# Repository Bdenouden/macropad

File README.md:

# macropad
This repo contains the design files for a macro pad based on 
- [https://www.thingiverse.com/thing:4765312](https://www.thingiverse.com/thing:4765312)
- [https://www.thingiverse.com/thing:4605764](https://www.thingiverse.com/thing:4605764)

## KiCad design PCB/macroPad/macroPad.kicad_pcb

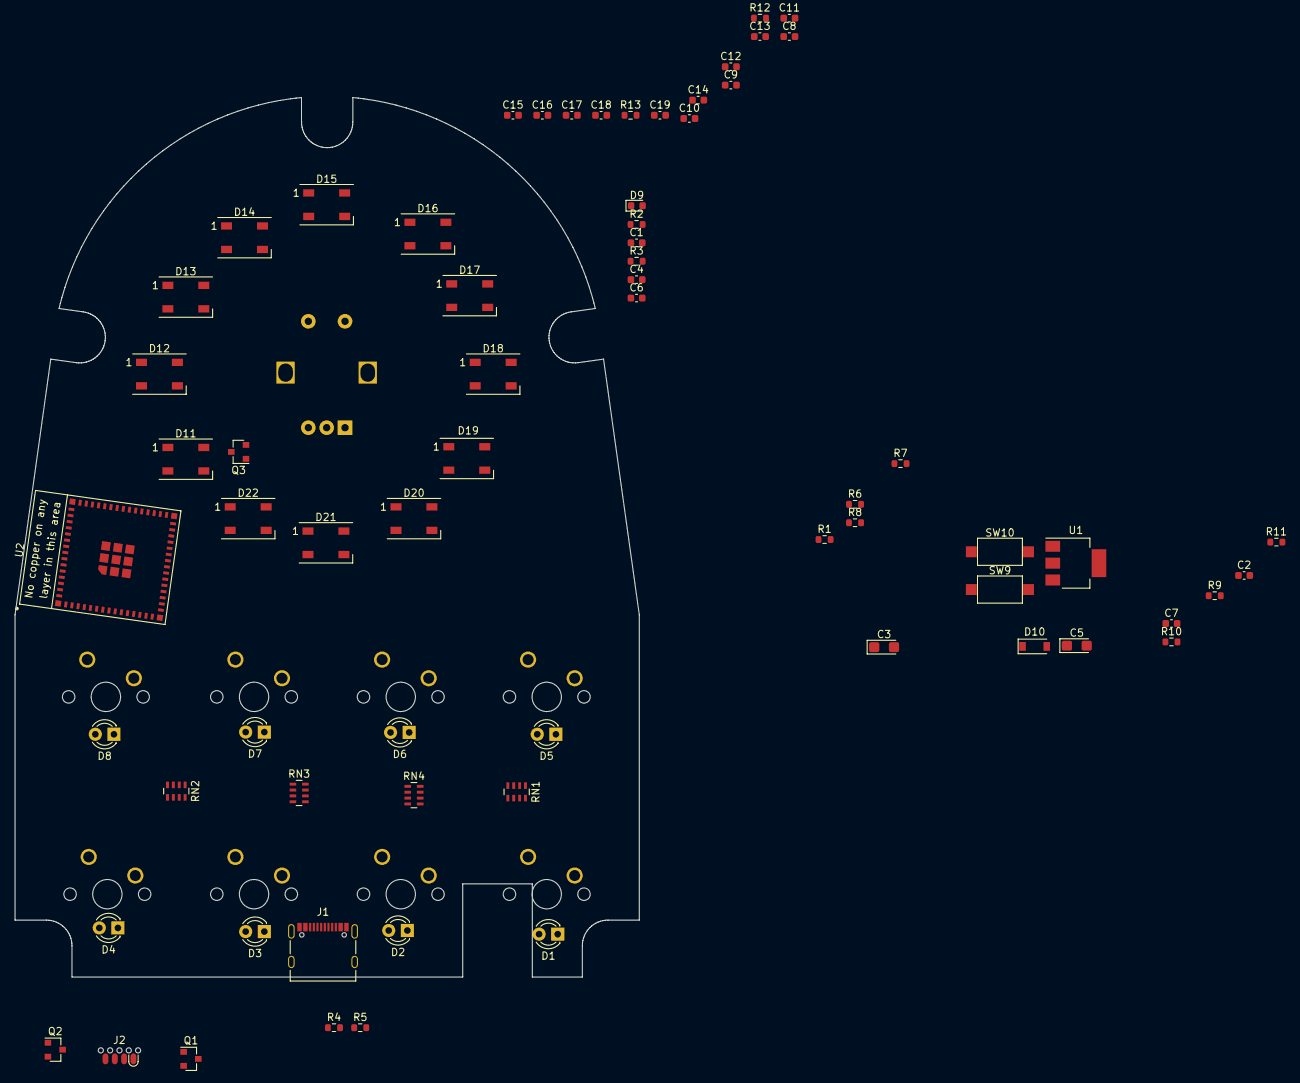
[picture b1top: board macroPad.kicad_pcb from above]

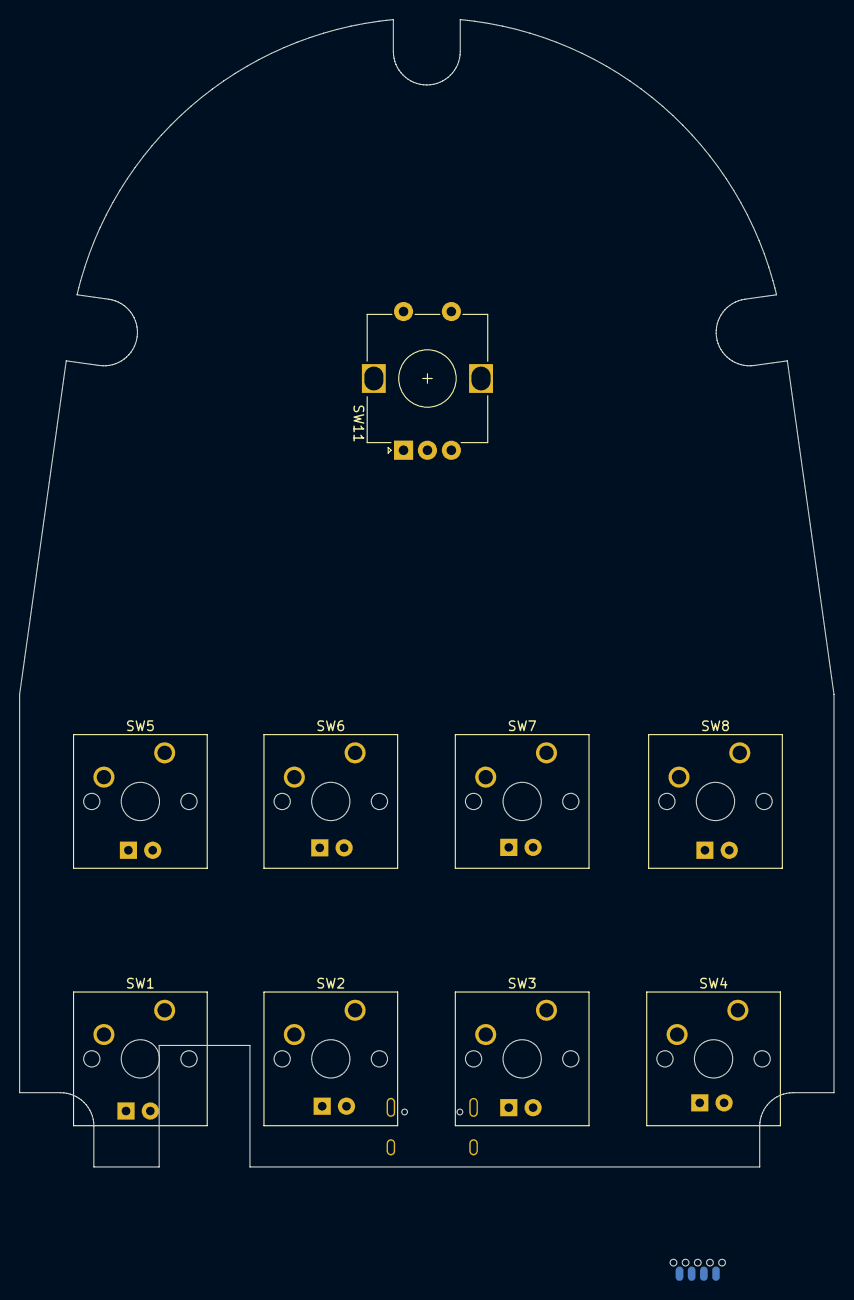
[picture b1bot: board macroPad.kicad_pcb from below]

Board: 2 copper layers, 85.1 x 119.9 mm, 76 parts (9 on the bottom side), 61 nets, no tracks yet.

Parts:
C1, C2, C6, C7: 0.1uF; C_0603_1608Metric
C3, C5: 22uF; CP_EIA-3216-10_Kemet-I
C4: 22uF; C_0603_1608Metric
C8, C9, C10, C11, C12, C13, C14, C15, C16, C17, C18, C19: 100nF; C_0603_1608Metric
D1, D2, D3, D4, D5, D6, D7, D8: LED; LED_D3.0mm
D9: POWER; LED_0603_1608Metric
D10: BAT760-7; D_SOD-123
D11, D12, D13, D14, D15, D16, D17, D18, D19, D20, D21, D22: WS2812B; LED_WS2812B_PLCC4_5.0x5.0mm_P3.2mm
J1: USB_C_Receptacle_USB2.0; USB_C_Receptacle_Palconn_UTC16-G
J2: SoicBite; SOIC_clipProgSmall
Q1, Q2: SS8050-G; SOT-23
Q3: BSS138; SOT-23
R1: 47; R_0603_1608Metric
R2, R3, R6, R9, R10, R12, R13: 10k; R_0603_1608Metric
R4, R5: 5k1; R_0603_1608Metric
R7, R8, R11: 100k; R_0603_1608Metric
RN1, RN2: 8R2; R_Array_Concave_4x0603
RN3, RN4: 10k; R_Array_Concave_4x0603
SW1, SW2, SW3, SW4, SW5, SW6, SW7, SW8: SW_cherry; SW_Cherry_MX_1.00u_PCB
SW9, SW10: SW_Push; SW_SPST_CK_RS282G05A3
SW11: Rotary_Encoder_Switch; RotaryEncoder_Alps_EC12E-Switch_Vertical_H20mm
U1: AMS1117-3.3; SOT-223-3_TabPin2
U2: ESP32-S2-MINI-1

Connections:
+3V3: C4.1, C5.1, C6.1, D1.2, D2.2, D3.2, D4.2, D5.2, D6.2, D7.2, D8.2, J2.1, Q3.1, R1.1, R6.2, R11.1, R12.2, SW1.1, SW2.1, SW3.1, SW4.1, SW5.2, SW6.2, SW7.2, SW8.2, U1.2, U2.3
/DTR: J2.5, Q2.3, R9.2
/EN: Q1.2, R2.1, U2.45
/IO0: C7.1, Q2.2, R3.1, R6.1, U2.4
/K1: RN4.1, SW1.2, U2.19
/K2: RN4.2, SW2.2, U2.15
/K3: RN4.3, SW3.2, U2.11
/K4: RN4.4, SW4.2, U2.7
/K5: RN3.8, SW5.1, U2.17
/K6: RN3.7, SW6.1, U2.13
/K7: RN3.6, SW7.1, U2.9
/K8: RN3.5, SW8.1, U2.5
/L1: RN1.8, U2.20
/L2: RN1.7, U2.16
/L3: RN1.6, U2.12
/L4: RN1.5, U2.8
/L5: RN2.8, U2.18
/L6: RN2.7, U2.14
/L7: RN2.6, U2.10
/L8: RN2.5, U2.6
/LED_DATA: Q3.2, R12.1
/ROT_CLK: R7.2, U2.32
/ROT_DT: R8.2, U2.33
/ROT_SW: R11.2, SW11.S1, U2.31
/RTS: J2.8, Q1.3, R10.2
/RX: J2.7, U2.40
/TX: J2.6, U2.39
/USB_D+: J1.A6, J1.B6, J2.3, U2.24
/USB_D-: J1.A7, J1.B7, J2.2, U2.23
/VBUS: C3.1, C8.1, C9.1, C10.1, C11.1, C12.1, C13.1, C14.1, C15.1, C16.1, C17.1, C18.1, C19.1, D10.1, D11.1, D12.1, D13.1, D14.1, D15.1, D16.1, D17.1, D18.1, D19.1, D20.1, D21.1, D22.1, R13.2, U1.3
/ledring/DIN_VCC: D11.4, Q3.3, R13.1
GND: C1.1, C2.1, C3.2, C4.2, C5.2, C6.2, C7.2, C8.2, C9.2, C10.2, C11.2, C12.2, C13.2, C14.2, C15.2, C16.2, C17.2, C18.2, C19.2, D9.1, D11.3, D12.3, D13.3, D14.3, D15.3, D16.3, D17.3, D18.3, D19.3, D20.3, D21.3, D22.3, J1.A1, J1.A12, J1.B1, J1.B12, J2.4, R4.1, R5.1, RN3.1, RN3.2, RN3.3, RN3.4, RN4.5, RN4.6, RN4.7, RN4.8, SW9.1, SW10.1, SW11.C, SW11.S2, U1.1, U2.1, U2.2, U2.30, U2.42, U2.43, U2.46, U2.47, U2.48, U2.49, U2.50, U2.51, U2.52, U2.53, U2.54, U2.55, U2.56, U2.57, U2.58, U2.59, U2.60, U2.61, U2.62, U2.63, U2.64, U2.65
unnamed: C1.2, R2.2, SW9.2
unnamed: C2.2, R3.2, SW10.2
unnamed: D1.1, RN1.1
unnamed: D2.1, RN1.2
unnamed: D3.1, RN1.3
unnamed: D4.1, RN1.4
unnamed: D5.1, RN2.1
unnamed: D6.1, RN2.2
unnamed: D7.1, RN2.3
unnamed: D8.1, RN2.4
unnamed: D9.2, R1.2
unnamed: D10.2, J1.A4, J1.A9, J1.B4, J1.B9
unnamed: D11.2, D13.4
unnamed: D12.4, D14.2
unnamed: D13.2, D15.4
unnamed: D14.4, D16.2
unnamed: D15.2, D17.4
unnamed: D16.4, D18.2
unnamed: D17.2, D19.4
unnamed: D18.4, D20.2
unnamed: D19.2, D21.4
unnamed: D20.4, D22.2
unnamed: D21.2, D22.4
unnamed: J1.A5, R4.2
unnamed: J1.B5, R5.2
unnamed: Q1.1, R9.1
unnamed: Q2.1, R10.1
unnamed: R7.1, SW11.A
unnamed: R8.1, SW11.B
